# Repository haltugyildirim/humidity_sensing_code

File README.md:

# humidity_sensing_setup
Humidity Sensing Setup For Graphene Studies. LabView and Arduino IDE codes with PCB files of electronics.

The files in this repository are for graphene atmosphere interaction project that held in Nanoscale Surface Science Laboratoryin Istanbul Technical University, Istanbul. This work is also the part of B.Sc. thesis of me. The project is suported by Tübitak 1003 project with the grant number of 114F036.

The files consist three parts; Arduino IDE codes, LabView codes and PCB files for electronics. The purposes of these files will
be listed further.

In order to observe effects of the atmospheric events on graphene, we created an isolated chamber with variance of humidity, 
pressure and temperature levels. In order to measure these quantities a SHT75 humidity temperature sensor, a BME280 pressure 
sensor and MAX31855 thermocouple sensor used with an arduino. The data comes from these sensors are read from serial port with 
the code written in Arduino IDE with corresponding libraries of the sensors. In order to prevet the wire chaos, a shield for
Arduino designed. A LabView code reads the serial port and plots the real tie graph of the temperature data that comes from the
thermocouple, humidity, pressure and atmospheric temperature. Also the resistivity of graphene sample is measured with a Keithley
2400 SourceMeter and this sourcemeter is controlled with the LabView code and readouts are plotted with LabView. 

For further information you can contact with me;
haltugyildirim_at_protonmail.com

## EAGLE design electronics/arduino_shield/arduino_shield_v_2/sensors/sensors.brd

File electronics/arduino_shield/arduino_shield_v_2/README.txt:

This new shield is called; Olla Tlaloc to reference the Aztec God of Weather Tlaloc. Olla means Jar in Spanish.

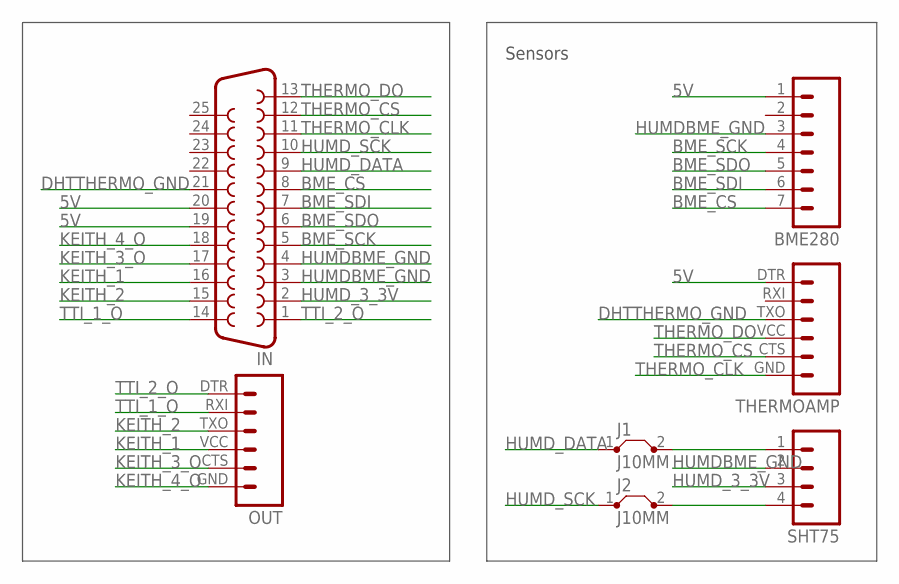
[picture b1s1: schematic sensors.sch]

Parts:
BME280: M07; 1X07
IN: F25HP
J1, J2: J10MM; 10
OUT: M06SIP; 1X06
SHT75: M04SMD_LONG; 1X04-SMD_LONG
THERMOAMP: M06SIP; 1X06

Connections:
5V: BME280.1, IN.19, IN.20, THERMOAMP.DTR (1)
BME_CS: BME280.7, IN.8
BME_SCK: BME280.4, IN.5
BME_SDI: BME280.6, IN.7
BME_SDO: BME280.5, IN.6
DHTTHERMO_GND: IN.21, THERMOAMP.TXO (3)
HUMDBME_GND: BME280.3, IN.3, IN.4, SHT75.2
HUMD_3_3V: IN.2, SHT75.3
HUMD_DATA: IN.9, J1.1
HUMD_SCK: IN.10, J2.1
KEITH_1: IN.16, OUT.VCC (4)
KEITH_2: IN.15, OUT.TXO (3)
KEITH_3_O: IN.17, OUT.CTS (5)
KEITH_4_O: IN.18, OUT.GND (6)
unnamed: J1.2, SHT75.1
unnamed: J2.2, SHT75.4
THERMO_CLK: IN.11, THERMOAMP.GND (6)
THERMO_CS: IN.12, THERMOAMP.CTS (5)
THERMO_DO: IN.13, THERMOAMP.VCC (4)
TTI_1_O: IN.14, OUT.RXI (2)
TTI_2_O: IN.1, OUT.DTR (1)

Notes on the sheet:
Sensors

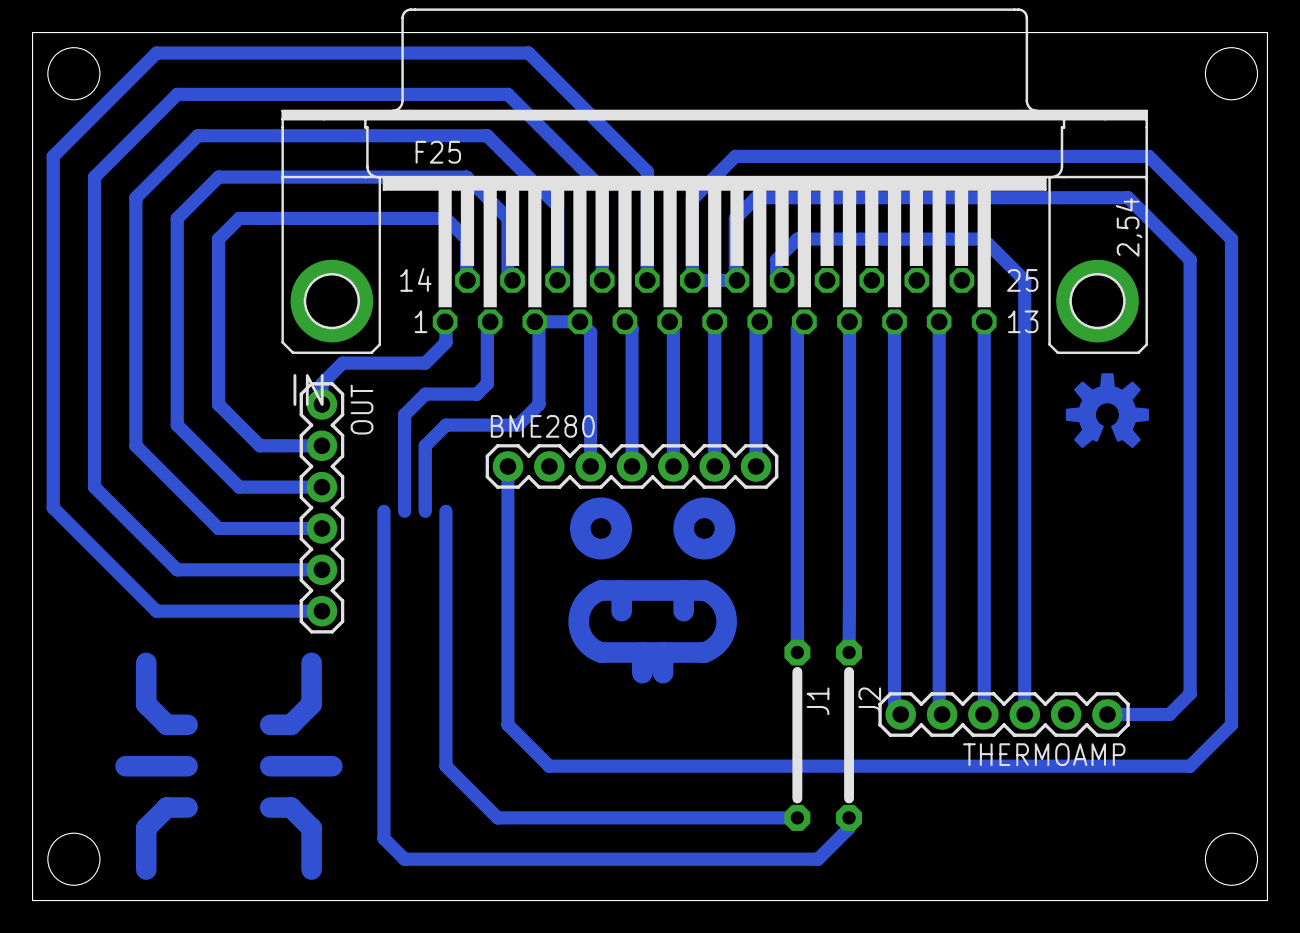
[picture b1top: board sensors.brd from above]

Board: 2 copper layers, 75.9 x 53.3 mm, 8 parts (1 on the bottom side), 21 nets.

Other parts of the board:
U$1: OSHW-LOGO-M

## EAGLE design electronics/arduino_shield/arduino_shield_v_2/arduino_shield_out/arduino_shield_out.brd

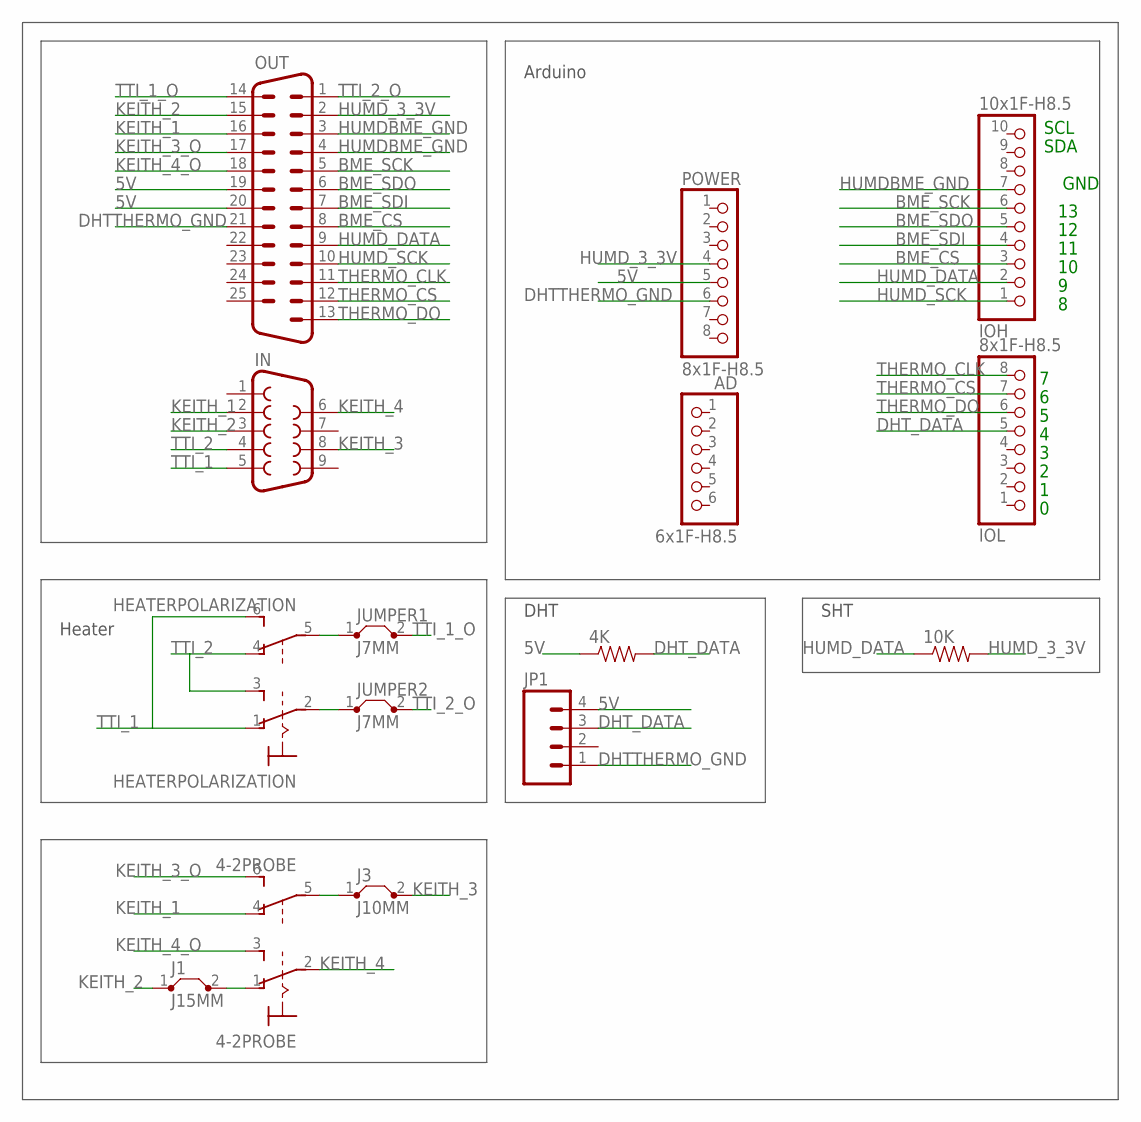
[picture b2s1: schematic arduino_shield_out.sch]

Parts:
4-2PROBE: M9040P2
4K: RESISTORPTH-1/2W; AXIAL-0.5
10K: RESISTORKIT; AXIAL-0.3-KIT
AD: 6x1F-H8.5; 1X06
HEATERPOLARIZATION: M9040P2
IN: DB9FEMALE; DB9
IOH: 10x1F-H8.5; 1X10
IOL: 8x1F-H8.5; 1X08
J1: J15MM; 15
J3: J10MM; 10
JP1: M04PTH; 1X04
JUMPER1, JUMPER2: J7MM; 07
OUT: DB25V; M25V
POWER: 8x1F-H8.5; 1X08

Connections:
5V: 4K.P$1 (1), JP1.4, OUT.19, OUT.20, POWER.5
BME_CS: IOH.3, OUT.8
BME_SCK: IOH.6, OUT.5
BME_SDI: IOH.4, OUT.7
BME_SDO: IOH.5, OUT.6
DHTTHERMO_GND: JP1.1, OUT.21, POWER.6
DHT_DATA: 4K.P$2 (2), IOL.5, JP1.3
HUMDBME_GND: IOH.7, OUT.3, OUT.4
HUMD_3_3V: 10K.P$2 (2), OUT.2, POWER.4
HUMD_DATA: 10K.P$1 (1), IOH.2, OUT.9
HUMD_SCK: IOH.1, OUT.10
KEITH_1: 4-2PROBE.4 (O), IN.2, OUT.16
KEITH_2: IN.3, J1.1, OUT.15
KEITH_3: IN.8, J3.2
KEITH_3_O: 4-2PROBE.6 (S), OUT.17
KEITH_4: 4-2PROBE.2, IN.6
KEITH_4_O: 4-2PROBE.3 (S), OUT.18
unnamed: HEATERPOLARIZATION.5, JUMPER1.1
unnamed: HEATERPOLARIZATION.2, JUMPER2.1
unnamed: 4-2PROBE.1 (O), J1.2
unnamed: 4-2PROBE.5, J3.1
THERMO_CLK: IOL.8, OUT.11
THERMO_CS: IOL.7, OUT.12
THERMO_DO: IOL.6, OUT.13
TTI_1: HEATERPOLARIZATION.1 (O), HEATERPOLARIZATION.6 (S), IN.5
TTI_1_O: JUMPER1.2, OUT.14
TTI_2: HEATERPOLARIZATION.3 (S), HEATERPOLARIZATION.4 (O), IN.4
TTI_2_O: JUMPER2.2, OUT.1

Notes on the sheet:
SDA
SCL
GND
Arduino
DHT
SHT
Heater

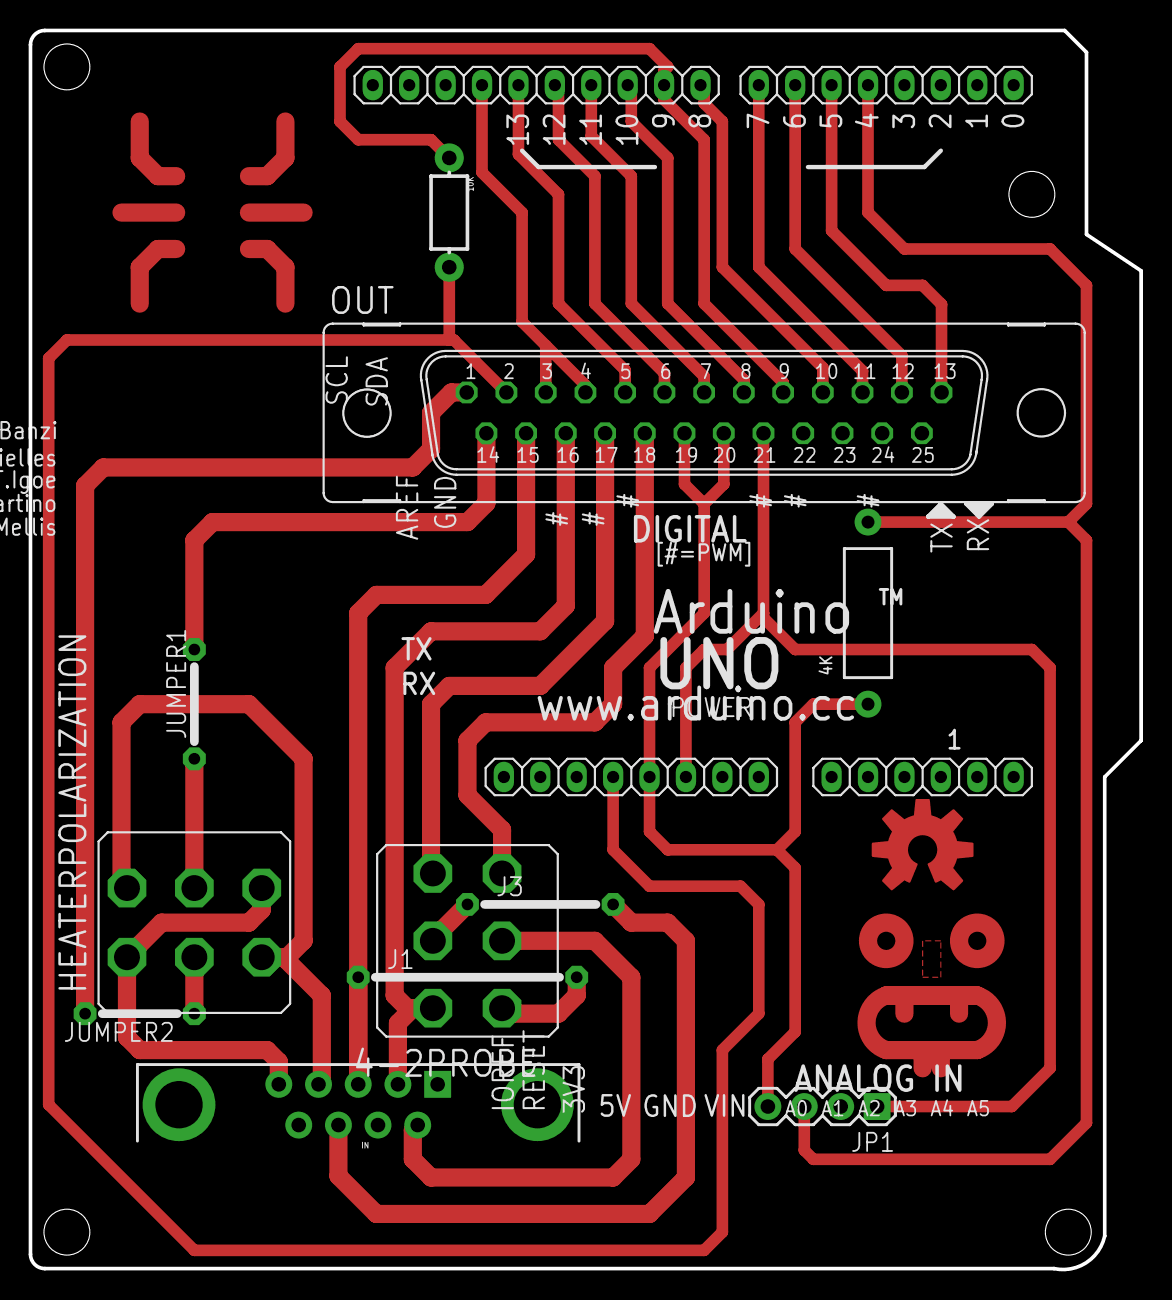
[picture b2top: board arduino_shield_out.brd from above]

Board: 2 copper layers, 77.5 x 86.4 mm, 16 parts (0 on the bottom side), 28 nets.

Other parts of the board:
U$1: OSHW-LOGO-L

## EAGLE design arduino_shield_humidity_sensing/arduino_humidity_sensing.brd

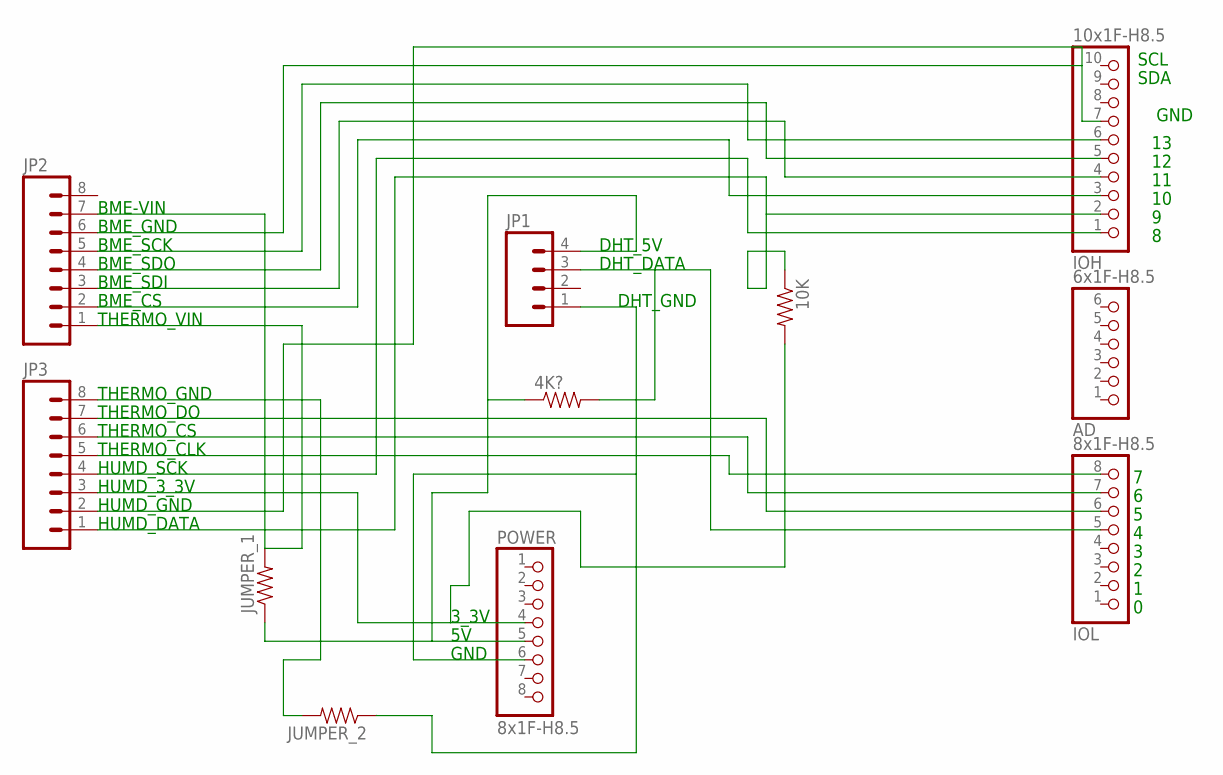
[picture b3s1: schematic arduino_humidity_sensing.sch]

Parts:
4K?: RESISTORPTH-1/2W; AXIAL-0.5
10K: RESISTORKIT; AXIAL-0.3-KIT
AD: 6x1F-H8.5; 1X06
IOH: 10x1F-H8.5; 1X10
IOL: 8x1F-H8.5; 1X08
JP1: M04PTH; 1X04
JP2, JP3: M08NO_SILK; 1X08_NO_SILK
JUMPER_1, JUMPER_2: RESISTORKIT; AXIAL-0.3-KIT
POWER: 8x1F-H8.5; 1X08

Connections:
unnamed: 4K?.P$2 (2), IOL.5, JP1.3
unnamed: 4K?.P$1 (1), JP1.4, JUMPER_1.P$1 (1), POWER.5
unnamed: JP1.1, JUMPER_2.P$1 (1), POWER.6
unnamed: 10K.P$1 (1), IOH.2, JP3.1
unnamed: IOH.1, JP3.4
unnamed: IOL.8, JP3.5
unnamed: IOL.7, JP3.6
unnamed: IOL.6, JP3.7
unnamed: IOH.4, JP2.3
unnamed: IOH.5, JP2.4
unnamed: IOH.3, JP2.2
unnamed: IOH.6, JP2.5
unnamed: IOH.7, JP2.6, JP3.2
unnamed: JP2.1, JP2.7, JUMPER_1.P$2 (2)
unnamed: JP3.8, JUMPER_2.P$2 (2)
unnamed: 10K.P$2 (2), JP3.3, POWER.4

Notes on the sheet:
SDA
SCL
BME-VIN
BME_GND
BME_SCK
BME_SDO
BME_SDI
BME_CS
THERMO_VIN
THERMO_GND
THERMO_DO
THERMO_CS
THERMO_CLK
HUMD_SCK
HUMD_3_3V
HUMD_GND
HUMD_DATA
GND
3_3V
DHT_GND
DHT_DATA
DHT_5V

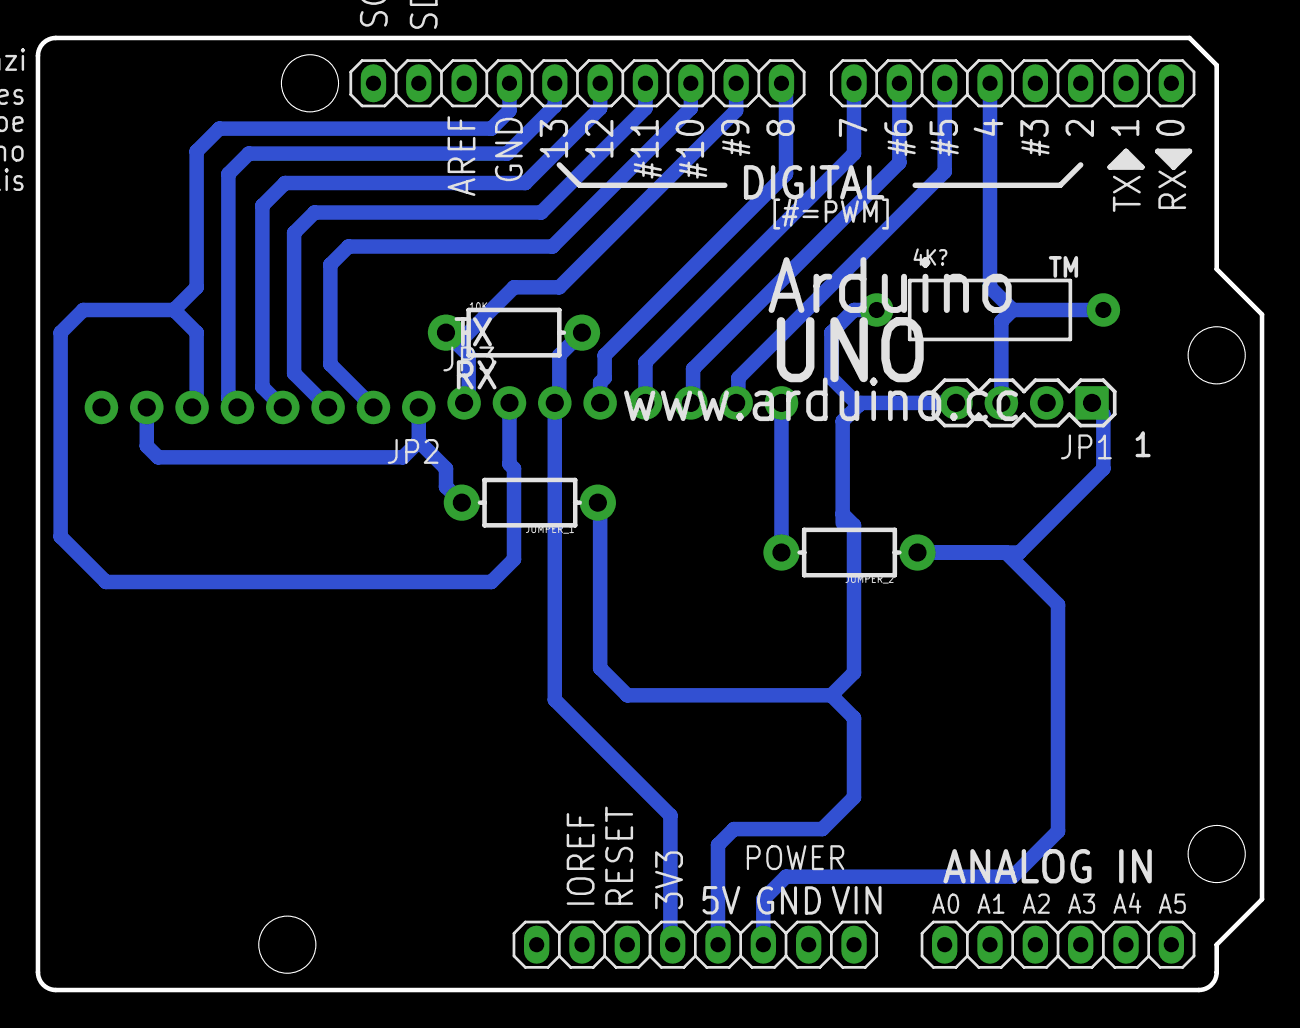
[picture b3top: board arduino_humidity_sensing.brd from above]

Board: 2 copper layers, 68.6 x 53.3 mm, 11 parts (0 on the bottom side), 16 nets.

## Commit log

2016-08-26 :tada: Added .gitattributes & .gitignore files
2016-08-26 adding the initial codes
    codes of arduino IDE and LabView
2016-08-26 adding PCB files for arduino shield
    Arduino shield for data acquisiton
2016-08-27 adding finished product jpg
2016-08-28 add system general assembly model jpg
    add jpg files
2016-08-28 adding electronics schematics.
    adding jpg files
2016-12-06 new shield and general sum up
    new shield and general sum up
2016-12-06 further changes
2016-12-06 libraries added.
2016-12-06 change in hardware
2017-08-08 final
    final update. project finished

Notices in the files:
parts and their libraries:
SparkFun-Connectors: Licensing: Creative Commons ShareAlike 4.0 International - https://creativecommons.org/licenses/by-sa/4.0
